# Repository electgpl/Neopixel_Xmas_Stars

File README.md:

# Neopixel Xmas Stars

Productos adquiridos en:

Este es un proyecto con fines decorativos para Navidad y otros, Se trata de una estrella con 20 Leds inteligentes Neopixel (WS2812) el cual podremos controlar desde Arduino, ESP8266, ESP32, PIC, etc....
En este proyecto estamos usando el Footprint de Wemos D1 Mini (ESP8266), pero se podria cablear cualquier controlador ya que solo se utilizan tres pines de conexion +5V, GND, DataIn.

## IDEs
  - REQUIERE DE LA BIBLIOTECA DE ADAFRUIT "Adafruit_NeoPixel.h"
  - Arduino IDE
  - PlatformIO
  - AtmelStudio
  - y mas...
  
## Diseño y Desarrollo

> Diseñado en dos capas con SMD y THT
> Los componentes SMD son solamente los LEDs 5050 y los capacitores de filtrado (se pueden excluir)
> Los componentes THT son unicamente los pines de coneccion con el WEMOS D1.
>          
> Componentes adquiridos a muy bajo costo en [LCSC].
> PCB creado en [JLCPCB].
> Diseño realizado en [Eagle].

### Instalación

Todos los archivos se encuentran disponibles en este repositorio, diagramas, pcb, programas de ejemplo. etc...

### Pendientes

 - Código de ejemplo puede ser utilizado tanto en Arduino como en Wemos o ESP8266, aunque no se estan usando funciones WiFi.
 - Se pretende generar un nuevo codigo para ESP8266 aprovechando el control por WiFi (WiFiManager, Blynk, etc..)

License
----

MIT

**Free Software, Hell Yeah!**

[LCSC]: <https://lcsc.com/?from_code=PL20191029WJJJ>
[JLCPCB]: <https://jlcpcb.com/>
[Eagle]: <https://www.autodesk.com/products/eagle/overview>

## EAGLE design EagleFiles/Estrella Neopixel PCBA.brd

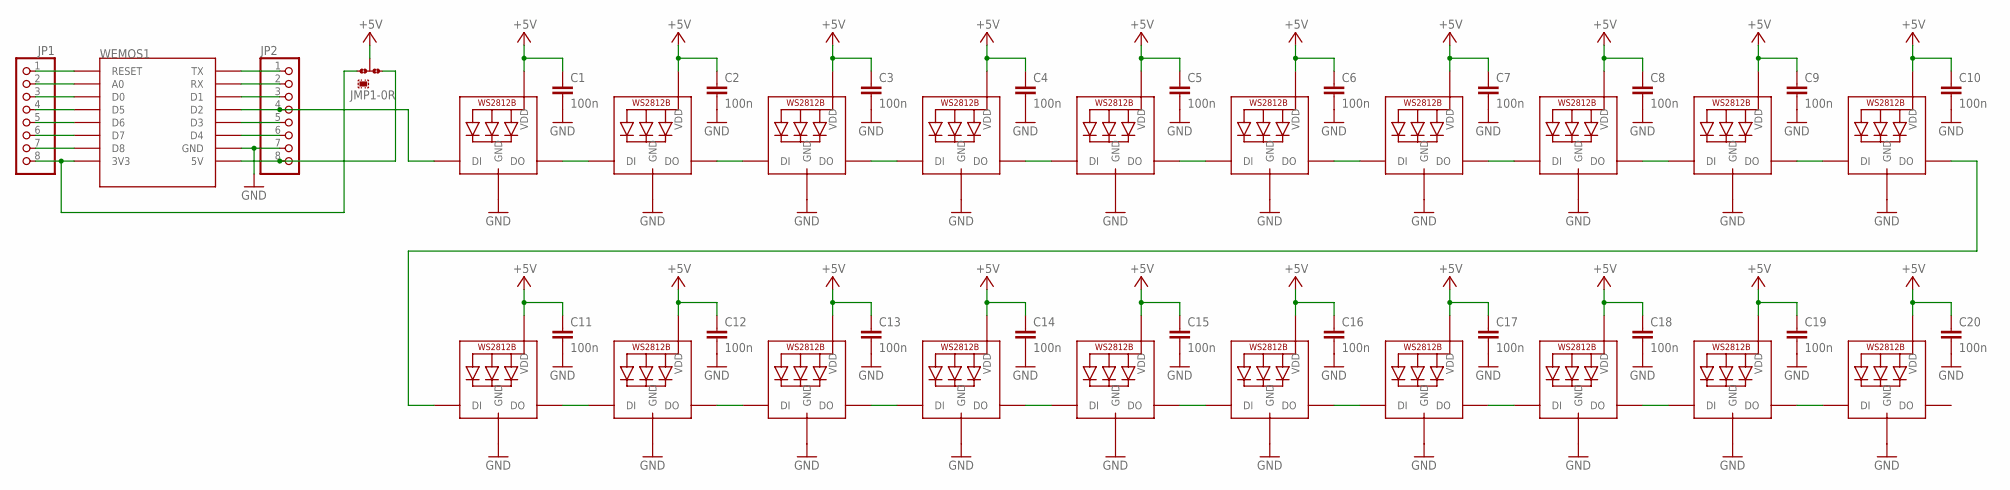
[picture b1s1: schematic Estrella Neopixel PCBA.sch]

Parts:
C1, C2, C3, C4, C5, C6, C7, C8, C9, C10, C11, C12, C13, C14, C15, C16, C17, C18, C19, C20: 100n; C0805K
JMP1: 0R-JUMPA; A0R-JMP
JP1, JP2: PINHD-1X8; 1X08
LED1, LED2, LED3, LED4, LED5, LED6, LED7, LED8, LED9, LED10, LED11, LED12, LED13, LED14, LED15, LED16, LED17, LED18, LED19, LED20: WS2812B_5050N; WS2812B-NARROW
WEMOS1: WEMOS-D1-MINI

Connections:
+5V: C1.1, C2.1, C3.1, C4.1, C5.1, C6.1, C7.1, C8.1, C9.1, C10.1, C11.1, C12.1, C13.1, C14.1, C15.1, C16.1, C17.1, C18.1, C19.1, C20.1, JMP1.2, LED1.1-VDD (VDD), LED2.1-VDD (VDD), LED3.1-VDD (VDD), LED4.1-VDD (VDD), LED5.1-VDD (VDD), LED6.1-VDD (VDD), LED7.1-VDD (VDD), LED8.1-VDD (VDD), LED9.1-VDD (VDD), LED10.1-VDD (VDD), LED11.1-VDD (VDD), LED12.1-VDD (VDD), LED13.1-VDD (VDD), LED14.1-VDD (VDD), LED15.1-VDD (VDD), LED16.1-VDD (VDD), LED17.1-VDD (VDD), LED18.1-VDD (VDD), LED19.1-VDD (VDD), LED20.1-VDD (VDD)
GND: C1.2, C2.2, C3.2, C4.2, C5.2, C6.2, C7.2, C8.2, C9.2, C10.2, C11.2, C12.2, C13.2, C14.2, C15.2, C16.2, C17.2, C18.2, C19.2, C20.2, JP2.7, LED1.3-GND (GND), LED2.3-GND (GND), LED3.3-GND (GND), LED4.3-GND (GND), LED5.3-GND (GND), LED6.3-GND (GND), LED7.3-GND (GND), LED8.3-GND (GND), LED9.3-GND (GND), LED10.3-GND (GND), LED11.3-GND (GND), LED12.3-GND (GND), LED13.3-GND (GND), LED14.3-GND (GND), LED15.3-GND (GND), LED16.3-GND (GND), LED17.3-GND (GND), LED18.3-GND (GND), LED19.3-GND (GND), LED20.3-GND (GND), WEMOS1.GND
unnamed: LED1.2-DOUT (DO), LED2.4-DIN (DI)
unnamed: LED2.2-DOUT (DO), LED3.4-DIN (DI)
unnamed: LED3.2-DOUT (DO), LED4.4-DIN (DI)
unnamed: LED4.2-DOUT (DO), LED5.4-DIN (DI)
unnamed: LED5.2-DOUT (DO), LED6.4-DIN (DI)
unnamed: LED6.2-DOUT (DO), LED7.4-DIN (DI)
unnamed: LED7.2-DOUT (DO), LED8.4-DIN (DI)
unnamed: LED8.2-DOUT (DO), LED9.4-DIN (DI)
unnamed: LED9.2-DOUT (DO), LED10.4-DIN (DI)
unnamed: LED10.2-DOUT (DO), LED11.4-DIN (DI)
unnamed: LED11.2-DOUT (DO), LED12.4-DIN (DI)
unnamed: LED12.2-DOUT (DO), LED13.4-DIN (DI)
unnamed: LED13.2-DOUT (DO), LED14.4-DIN (DI)
unnamed: LED14.2-DOUT (DO), LED15.4-DIN (DI)
unnamed: LED15.2-DOUT (DO), LED16.4-DIN (DI)
unnamed: JMP1.3, JP2.8, WEMOS1.5V
unnamed: JMP1.1, JP1.8, WEMOS1.3V3
unnamed: JP1.1, WEMOS1.RESET
unnamed: JP1.2, WEMOS1.A0
unnamed: JP1.3, WEMOS1.D0
unnamed: JP1.4, WEMOS1.D5
unnamed: JP1.5, WEMOS1.D6
unnamed: JP1.6, WEMOS1.D7
unnamed: JP1.7, WEMOS1.D8
unnamed: JP2.6, WEMOS1.D4
unnamed: JP2.5, WEMOS1.D3
unnamed: JP2.3, WEMOS1.D1
unnamed: JP2.2, WEMOS1.RX
unnamed: JP2.1, WEMOS1.TX
unnamed: JP2.4, LED1.4-DIN (DI), WEMOS1.D2
unnamed: LED17.2-DOUT (DO), LED18.4-DIN (DI)
unnamed: LED18.2-DOUT (DO), LED19.4-DIN (DI)
unnamed: LED19.2-DOUT (DO), LED20.4-DIN (DI)
unnamed: LED16.2-DOUT (DO), LED17.4-DIN (DI)

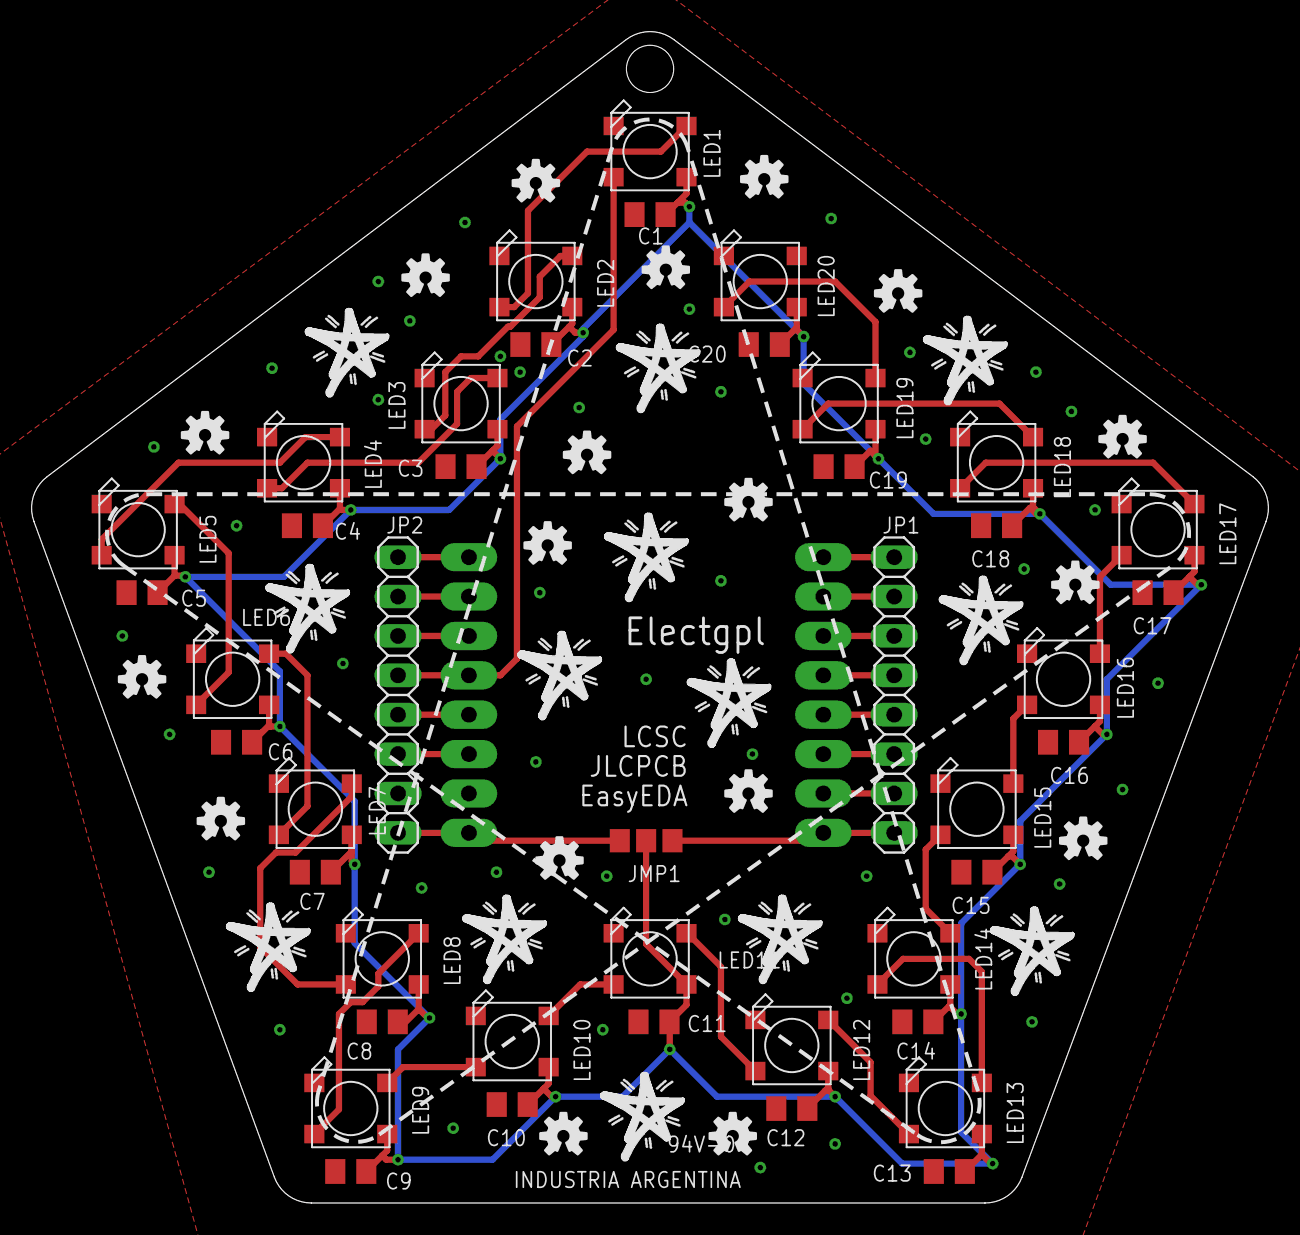
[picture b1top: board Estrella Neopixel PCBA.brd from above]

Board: 2 copper layers, 79.8 x 75.6 mm, 75 parts (1 on the bottom side), 36 nets.

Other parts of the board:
U$1, U$2, U$3, U$4, U$5, U$6, U$7, U$8, U$9, U$10, U$13, U$14, U$15: STARBOARD_LOGO
U$11, U$12, U$16, U$17, U$18, U$19, U$20, U$21, U$22, U$23, U$24, U$25, U$26, U$27, U$28, U$29, U$30, U$31: OSHW-LOGO-S

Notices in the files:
parts and their libraries:
SparkFun-Retired: Licensing:Creative Commons ShareAlike 4.0 International - https://creativecommons.org/licenses/by-sa/4.0
SparkFun-Aesthetics: Licensing: CC v3.0 Share-Alike You are welcome to use this library for commercial purposes.
